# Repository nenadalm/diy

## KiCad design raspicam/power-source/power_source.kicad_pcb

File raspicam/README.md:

# Raspicam

* security camera saving video on motion using raspberry pi

## How to

* install lite image of [Raspberry Pi OS][10]
* login into raspbian using default username ```pi``` and  password ```raspberry```
    * run ```$ sudo raspi-config```
        * enable i2c: "Interfacing Options"/I2C/Yes
        * enable ssh: "Interfacing Options"/SSH/Yes
    * reboot ```$ sudo reboot```
    * update system
    ``` $ sudo apt update && sudo apt full-upgrade -y```
* use another pc to configure the pi
    * copy ssh-key into the camera
    ```
    $ ssh-copy-id pi@<pi_ip_addr>
    ```
    * ssh into pi and copy the public key to be able to login as root
        $ sudo cp -R .ssh /root
    * configure all your raspberry pis used as cam in ```/etc/ansible/hosts```
    ```
    [raspicams]
    <ip_of_the_pi> ansible_connection=ssh ansible_ssh_user=root
    ```
    * let ansible to configure the rest (the command also serves for updating to the latest version of raspicam)
    ```
    $ ansible-playbook ./ansible/playbook2.yml
    ```
* make ir-cut filter switcher (subdirectory ir-switcher)
* make case (subdirectory case)
* wire everything and put that into camera case
* turn raspberry pi on and run ansible

## Suggested SW
* [kicad][5]
    * you will need it to show electric circuits and make printed circuit boards
* [openscad][7]
    * you will need it to 3d print boxes and holders
* [slic3r][8]
    * you will need it to create gcode for your 3d printer

## Required HW
* [raspberry pi 2 model b][1] which will be used to control camera and take videos on motion
* wifi adapter to be able to connect to your raspberry wirelessly
* [pi noir camera][9] which allows you to take videos even at night
* [ir cut filter][2] which will improve quality of your videos during day filtering out infrared radiation
* additional components to make [ir cut filter][9] turn on/off automatically based on luminosity
    * [2x opto relay][3]
    * 2x npn transistor
    * 2x 470R resistor
    * 2x 100R resistor
    * [light sensor][4]

* 3d printer to print boxes and holders for components

[1]: http://www.raspberrypi.org/products/raspberry-pi-2-model-b/
[2]: http://www.ebay.com/itm/Good-IR-CUT-CS-0-3-Day-Night-Filter-Switcher-8-2mm-C-CS60-J-F-for-Net-Machine-/181634220091?pt=LH_DefaultDomain_15&hash=item2a4a3e403b
[3]: https://www.gme.cz/img/cache/doc/523/189/epr212a408000z-datasheet-1.pdf
[4]: http://www.easyduino.cz/Senzor-intenzity-osvetleni-pro-Arduino-BH1750FVI-GY-302-d126.ht
[5]: http://www.kicad-pcb.org/display/KICAD/KiCad+EDA+Software+Suite
[7]: http://www.openscad.org/
[8]: http://slic3r.org/
[9]: https://www.raspberrypi.org/products/pi-noir-camera/
[10]: https://www.raspberrypi.com/software/

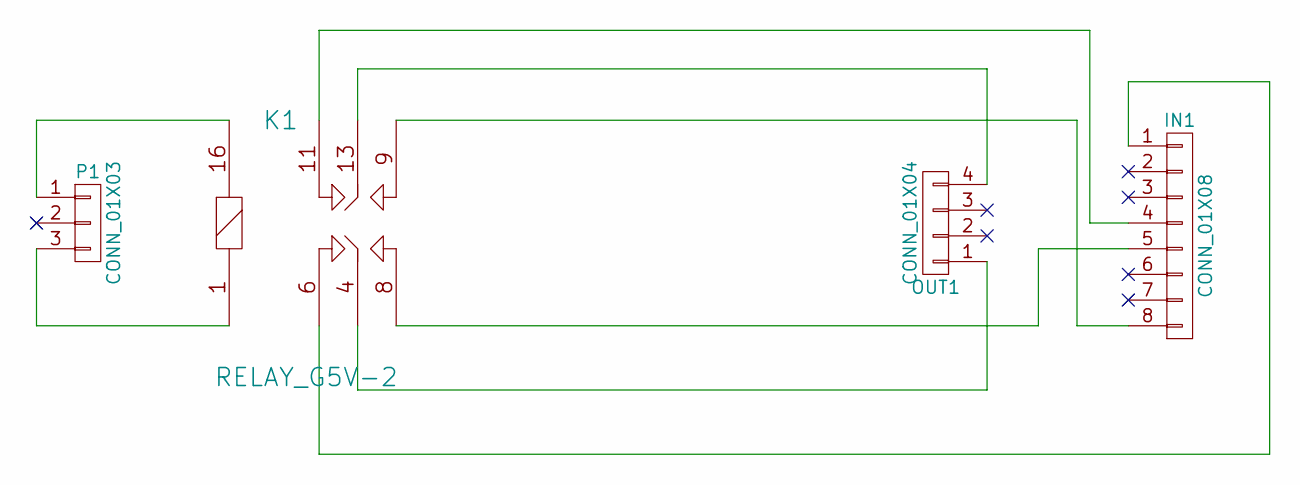
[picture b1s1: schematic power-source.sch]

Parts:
IN1: CONN_01X08; USB2AW
K1: RELAY_G5V-2; RELAY
OUT1: CONN_01X04; USB_A
P1: CONN_01X03; CMM_53SQ

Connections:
unnamed: IN1.1, K1.6
unnamed: IN1.4, K1.11
unnamed: IN1.5, K1.8
unnamed: IN1.8, K1.9
unnamed: K1.1, P1.3
unnamed: K1.4, OUT1.1
unnamed: K1.13, OUT1.4
unnamed: K1.16, P1.1

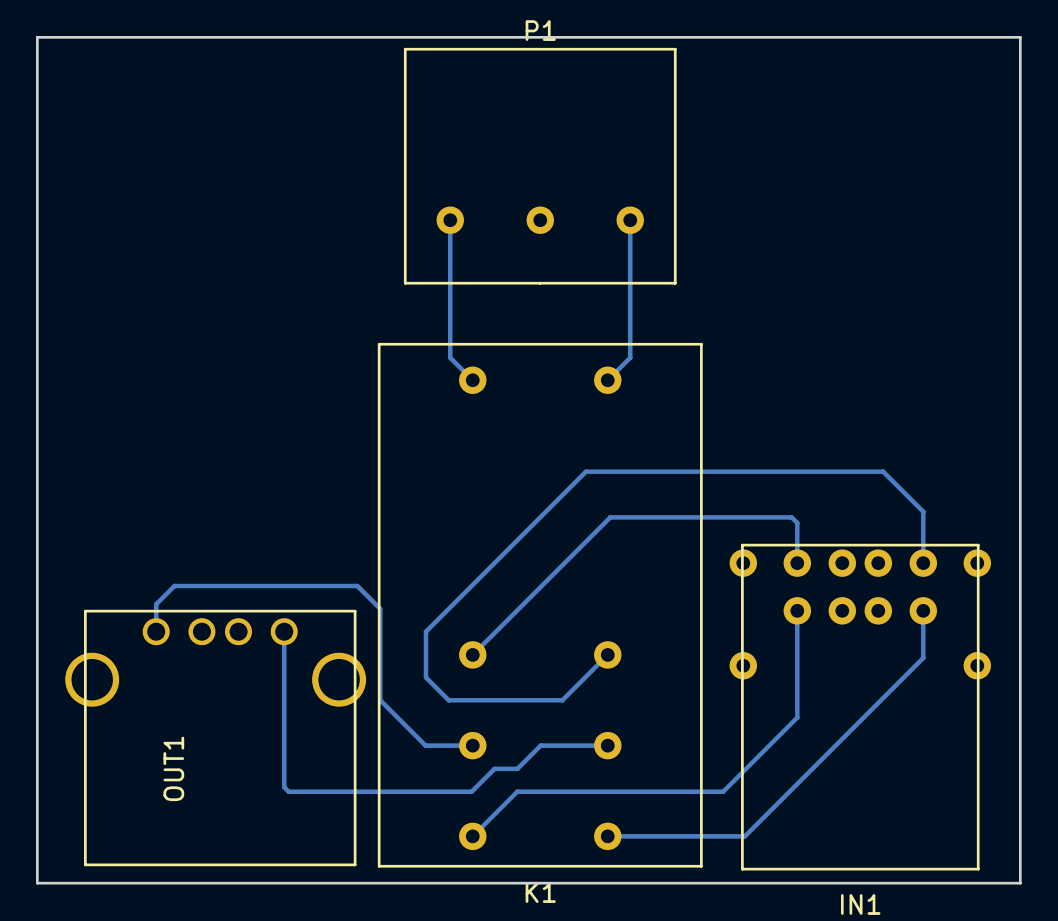
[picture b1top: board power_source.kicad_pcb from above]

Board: 2 copper layers, 54.6 x 47.0 mm, 4 parts (0 on the bottom side), 8 nets.

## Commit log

2015-09-03 Raspicam
2015-09-05 [Case]: Move holes higher so it's hopefully not necessary to use file
2015-09-30 Use hexo to generate pages
2015-11-02 Remove archive, change projects url so it doesn't change with regeneration
2016-11-26 Remove non functional links
2016-12-17 [raspicam]: Open in new version of KiCad
2017-03-18 [raspicam]: Add ansible playbook, update readme
2018-12-19 [raspicam]: Update configs
2020-06-13 [raspicam]: Keep records for 60 days
2020-06-13 [raspicam]: Restart motion if not working
2020-06-13 [raspicam]: Update network config
2020-09-03 [raspicamp]: Fix test if motion is running
    - handles active, exited service
2024-06-23 [raspicam] Update ansible config
2024-09-01 [raspicam] Enable watchdog + forgotten systemed services, update mounts
2025-04-03 [raspicam] Add header into each h264 frame
